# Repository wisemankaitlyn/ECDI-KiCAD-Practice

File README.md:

# KiCAD Practice with *Electronic Circuit Design Ideas*

I picked up an old textbook with a bunch of example circuits, and I'm using them to practice schematic and PCB layout with KiCAD.

1.  Digital Circuits
2.  Interface Circuits
3.  Timer Circuits
4.  Op-amp Circuits
5.  Amplifier Circuits
6.  Waveform Generators
7.  Phase-locked Loop Circuits
8.  Power Supply Circuits
9.  Voltage Regulator Circuits
10.  Battery Circuits
11.  Motor Control Circuits
12.  Encoders/Decoders
13.  Tester Circuits
14.  Miscellaneous Circuits

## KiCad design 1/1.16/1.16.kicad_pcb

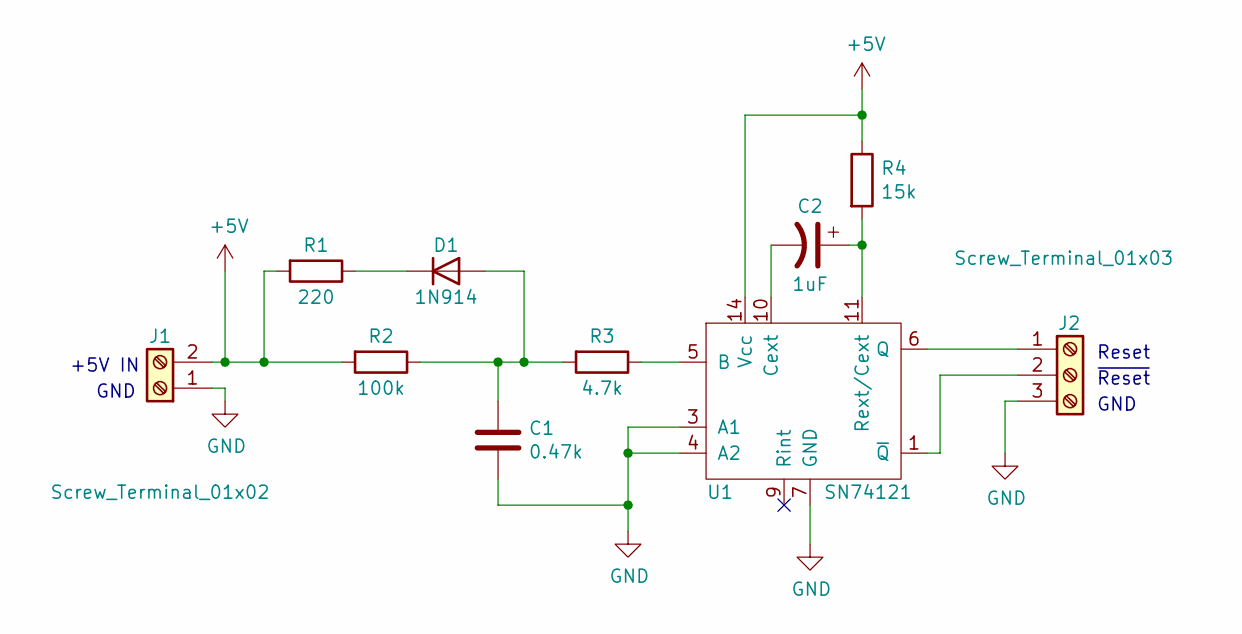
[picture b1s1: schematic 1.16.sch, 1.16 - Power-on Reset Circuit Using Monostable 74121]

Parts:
C1: 0.47k; C_Axial_L3.8mm_D2.6mm_P7.50mm_Horizontal
C2: 1uF; CP_Axial_L10.0mm_D4.5mm_P15.00mm_Horizontal
D1: 1N914; D_DO-35_SOD27_P7.62mm_Horizontal
J1: Screw_Terminal_01x02; TerminalBlock_bornier-2_P5.08mm
J2: Screw_Terminal_01x03; TerminalBlock_bornier-3_P5.08mm
R1: 220; R_Axial_DIN0207_L6.3mm_D2.5mm_P10.16mm_Horizontal
R2: 100k; R_Axial_DIN0207_L6.3mm_D2.5mm_P10.16mm_Horizontal
R3: 4.7k; R_Axial_DIN0207_L6.3mm_D2.5mm_P10.16mm_Horizontal
R4: 15k; R_Axial_DIN0207_L6.3mm_D2.5mm_P10.16mm_Horizontal
U1: SN74121; DIP-14_W7.62mm

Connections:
+5V: J1.2, R1.2, R2.2, R4.1, U1.14 (Vcc)
GND: C1.2, J1.1, J2.3, U1.3 (A1), U1.4 (A2), U1.7 (GND)
unnamed: C1.1, D1.2 (A), R2.1, R3.2
unnamed: C2.1, R4.2, U1.11 (Rext/Cext)
unnamed: C2.2, U1.10 (Cext)
unnamed: D1.1 (K), R1.1
unnamed: J2.1, U1.6 (Q)
unnamed: J2.2, U1.1 (~Q)
unnamed: R3.1, U1.5 (B)

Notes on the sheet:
+5V IN
GND
Reset
~Reset

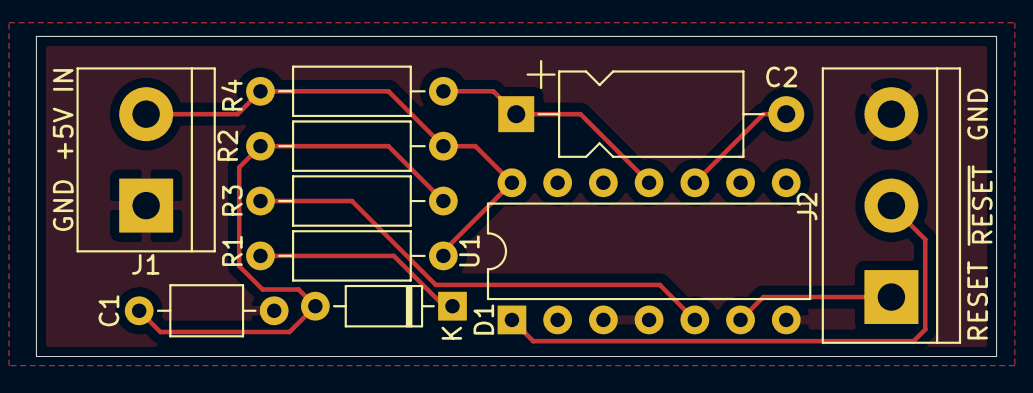
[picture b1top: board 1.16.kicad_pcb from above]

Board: 2 copper layers, 53.3 x 17.8 mm, 10 parts (0 on the bottom side), 9 nets.

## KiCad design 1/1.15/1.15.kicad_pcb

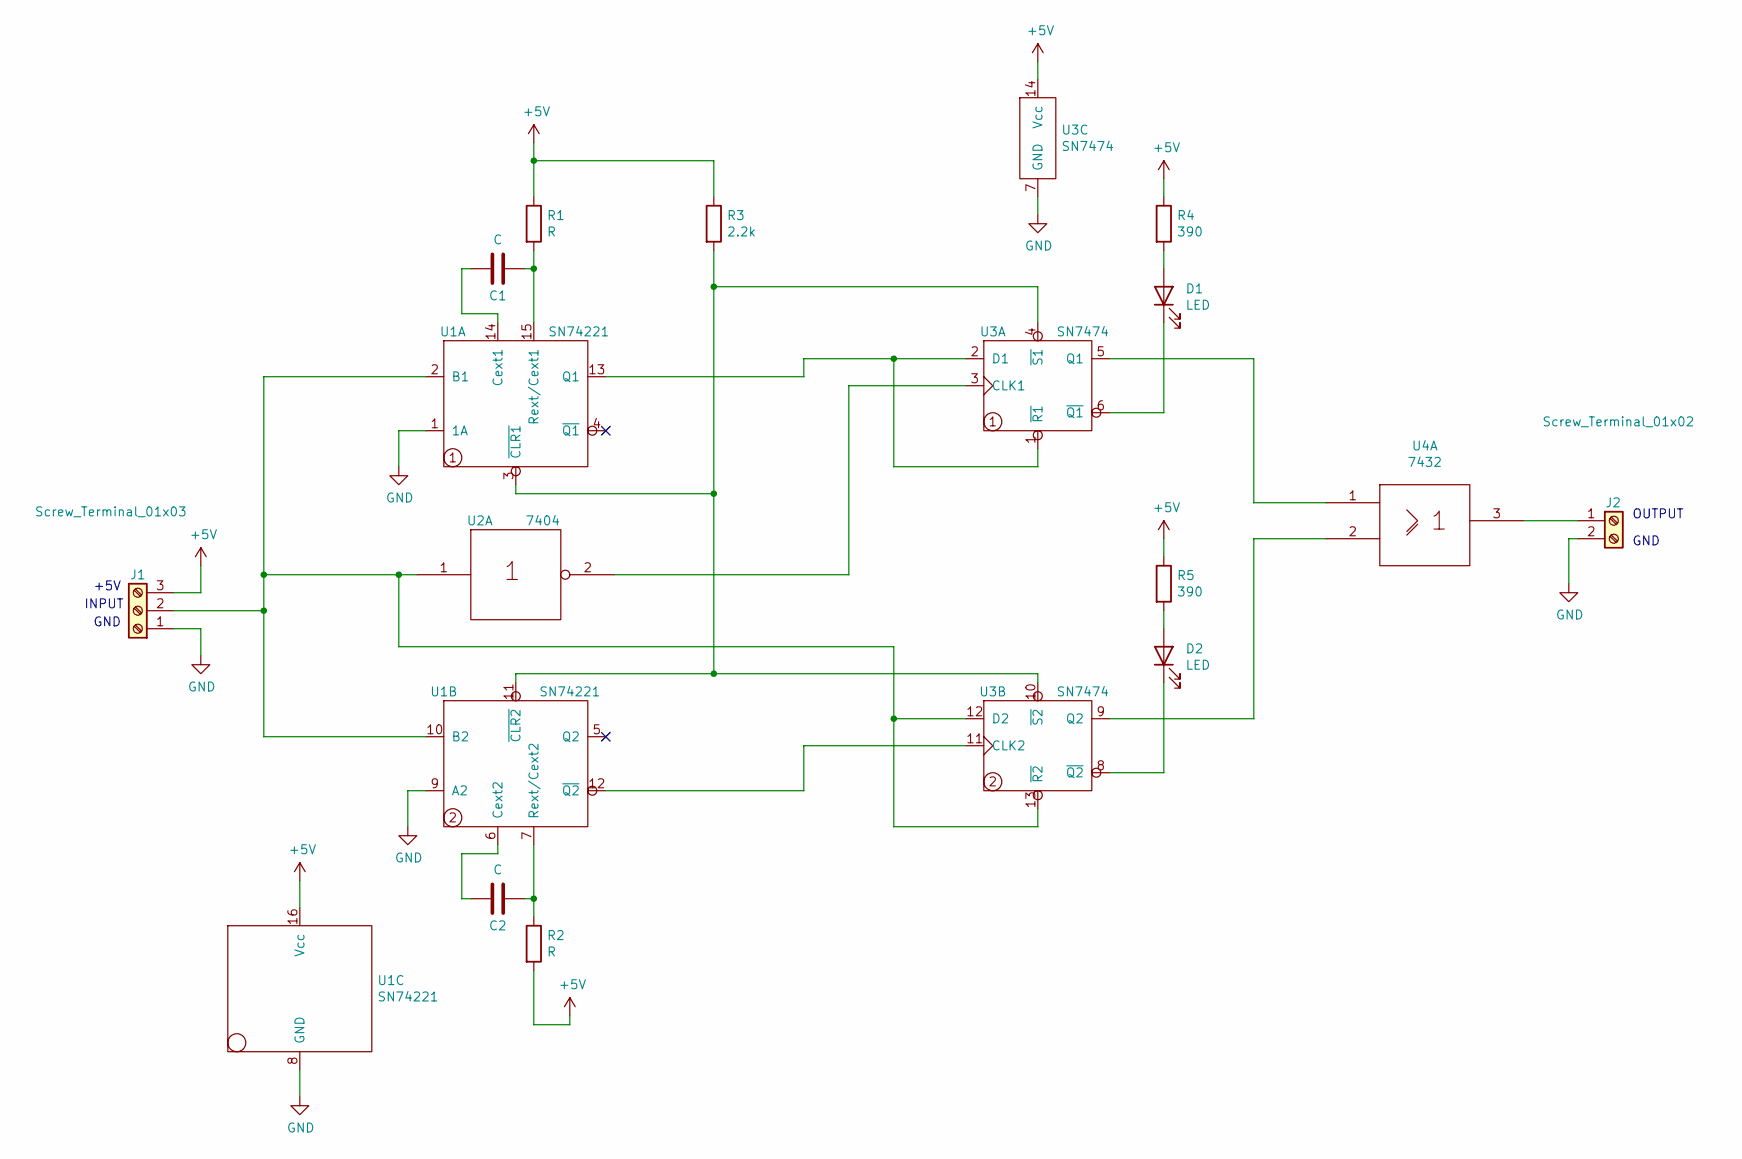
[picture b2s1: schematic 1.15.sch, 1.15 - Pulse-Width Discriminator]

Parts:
C1, C2: C; C_Axial_L3.8mm_D2.6mm_P7.50mm_Horizontal
D1, D2: LED; LED_D3.0mm
J1: Screw_Terminal_01x03; TerminalBlock_bornier-3_P5.08mm
J2: Screw_Terminal_01x02; TerminalBlock_bornier-2_P5.08mm
R1, R2: R; R_Axial_DIN0207_L6.3mm_D2.5mm_P10.16mm_Horizontal
R3: 2.2k; R_Axial_DIN0207_L6.3mm_D2.5mm_P10.16mm_Horizontal
R4, R5: 390; R_Axial_DIN0207_L6.3mm_D2.5mm_P10.16mm_Horizontal
U1: SN74221; DIP-16_W7.62mm
U2: 7404; DIP-14_W7.62mm
U3: SN7474; DIP-14_W7.62mm
U4: 7432; DIP-14_W7.62mm

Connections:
+5V: J1.3, R1.1, R2.2, R3.1, R4.1, R5.1, U1.16 (Vcc), U2.14 (Vcc), U3.14 (Vcc), U4.14 (Vcc)
GND: J1.1, J2.2, U1.1 (1A), U1.8 (GND), U1.9 (A2), U2.7 (Gnd), U3.7 (GND), U4.7 (Gnd)
unnamed: C1.1, R1.2, U1.15 (Rext/Cext1)
unnamed: C1.2, U1.14 (Cext1)
unnamed: C2.1, R2.1, U1.7 (Rext/Cext2)
unnamed: C2.2, U1.6 (Cext2)
unnamed: D1.1 (K), U3.6 (~Q1)
unnamed: D1.2 (A), R4.2
unnamed: D2.1 (K), U3.8 (~Q2)
unnamed: D2.2 (A), R5.2
unnamed: J1.2, U1.2 (B1), U1.10 (B2), U2.1, U3.12 (D2), U3.13 (~R2)
unnamed: J2.1, U4.3
unnamed: R3.2, U1.3 (~CLR1), U1.11 (~CLR2), U3.4 (~S1), U3.10 (~S2)
unnamed: U1.12 (~Q2), U3.11 (CLK2)
unnamed: U1.13 (Q1), U3.1 (~R1), U3.2 (D1)
unnamed: U2.2, U3.3 (CLK1)
unnamed: U3.5 (Q1), U4.1
unnamed: U3.9 (Q2), U4.2

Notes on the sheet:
+5V
INPUT
GND
OUTPUT

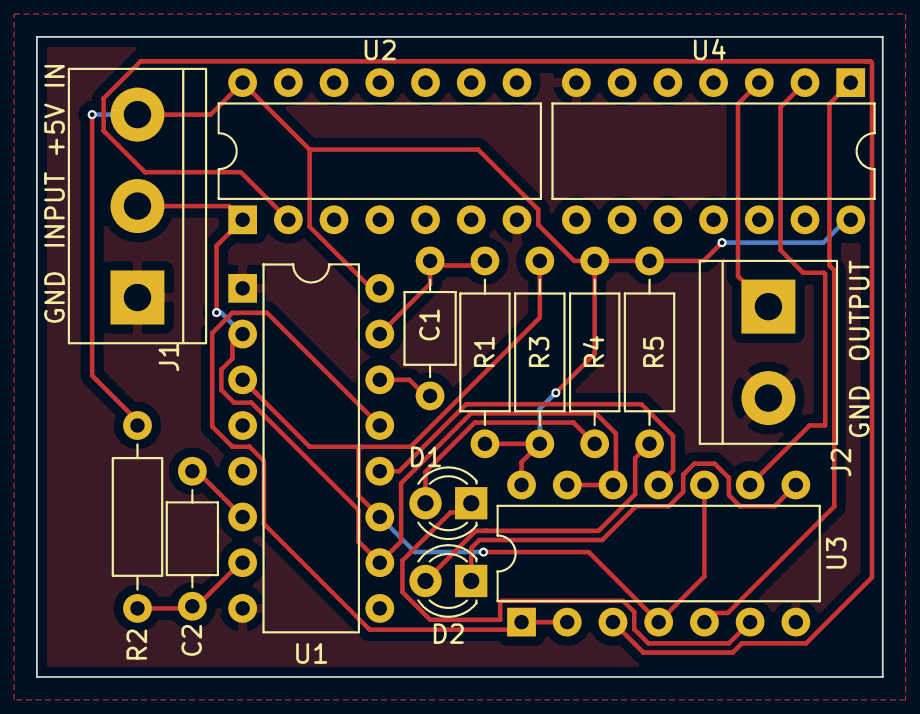
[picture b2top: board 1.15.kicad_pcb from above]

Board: 2 copper layers, 47.0 x 35.6 mm, 15 parts (0 on the bottom side), 18 nets.

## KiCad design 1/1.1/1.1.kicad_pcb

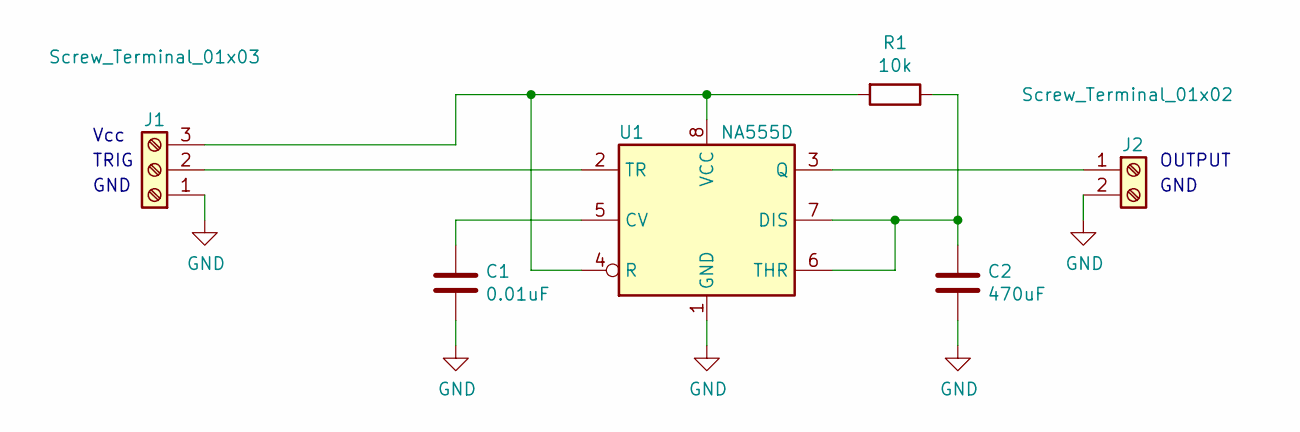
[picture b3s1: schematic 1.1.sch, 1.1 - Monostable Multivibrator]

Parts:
C1: 0.01uF; C_Axial_L5.1mm_D3.1mm_P10.00mm_Horizontal
C2: 470uF; C_Axial_L5.1mm_D3.1mm_P10.00mm_Horizontal
J1: Screw_Terminal_01x03; TerminalBlock_bornier-3_P5.08mm
J2: Screw_Terminal_01x02; TerminalBlock_bornier-2_P5.08mm
R1: 10k; R_Axial_DIN0207_L6.3mm_D2.5mm_P10.16mm_Horizontal
U1: NA555D; DIP-8_W7.62mm

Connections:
GND: C1.2, C2.2, J1.1, J2.2, U1.1 (GND)
unnamed: C1.1, U1.5 (CV)
unnamed: C2.1, R1.1, U1.6 (THR), U1.7 (DIS)
unnamed: J1.2, U1.2 (TR)
unnamed: J1.3, R1.2, U1.4 (R), U1.8 (VCC)
unnamed: J2.1, U1.3 (Q)

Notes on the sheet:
OUTPUT
GND
Vcc
TRIG

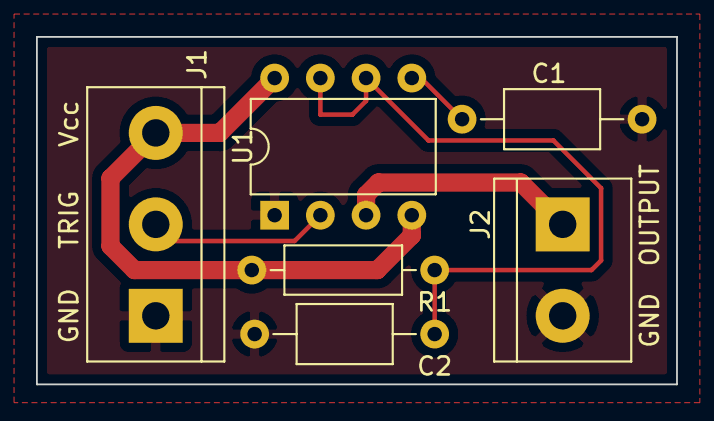
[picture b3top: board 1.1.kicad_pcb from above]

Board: 2 copper layers, 35.6 x 19.3 mm, 6 parts (0 on the bottom side), 6 nets.

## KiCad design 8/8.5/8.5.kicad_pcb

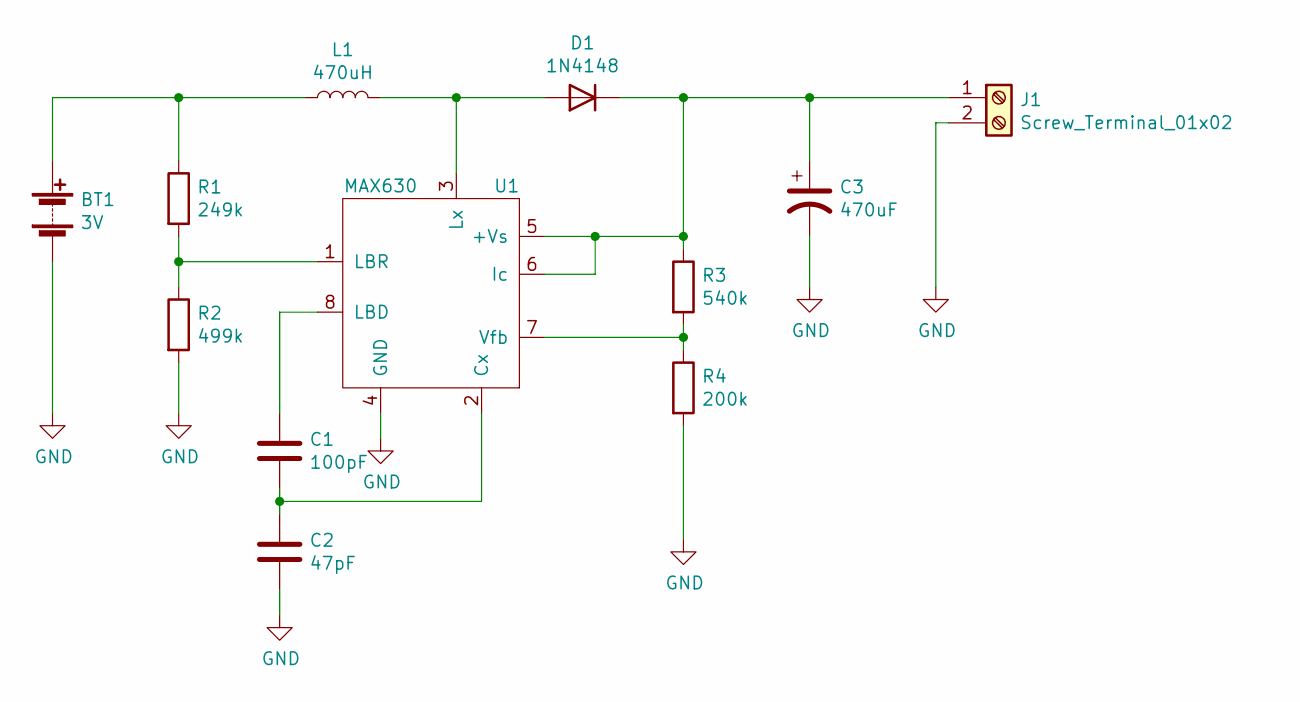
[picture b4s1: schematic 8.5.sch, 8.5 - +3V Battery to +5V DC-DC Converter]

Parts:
BT1: 3V; BatteryHolder_Keystone_1058_1x2032
C1: 100pF; C_Axial_L3.8mm_D2.6mm_P7.50mm_Horizontal
C2: 47pF; C_Axial_L3.8mm_D2.6mm_P7.50mm_Horizontal
C3: 470uF; C_Axial_L3.8mm_D2.6mm_P7.50mm_Horizontal
D1: 1N4148; D_DO-35_SOD27_P7.62mm_Horizontal
J1: Screw_Terminal_01x02; TerminalBlock_bornier-2_P5.08mm
L1: 470uH; L_Axial_L5.0mm_D3.6mm_P10.00mm_Horizontal_Murata_BL01RN1A2A2
R1: 249k; R_Axial_DIN0204_L3.6mm_D1.6mm_P5.08mm_Horizontal
R2: 499k; R_Axial_DIN0204_L3.6mm_D1.6mm_P5.08mm_Horizontal
R3: 540k; R_Axial_DIN0204_L3.6mm_D1.6mm_P5.08mm_Horizontal
R4: 200k; R_Axial_DIN0204_L3.6mm_D1.6mm_P5.08mm_Horizontal
U1: MAX630; MAX630CPA+_8-pin_CDIP

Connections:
GND: BT1.2 (-), C2.2, C3.2, J1.2, R2.2, R4.2, U1.4 (GND)
unnamed: BT1.1 (+), L1.1, R1.1
unnamed: C1.1, U1.8 (LBD)
unnamed: C1.2, C2.1, U1.2 (Cx)
unnamed: C3.1, D1.1 (K), J1.1, R3.1, U1.5 (+Vs), U1.6 (Ic)
unnamed: D1.2 (A), L1.2, U1.3 (Lx)
unnamed: R1.2, R2.1, U1.1 (LBR)
unnamed: R3.2, R4.1, U1.7 (Vfb)

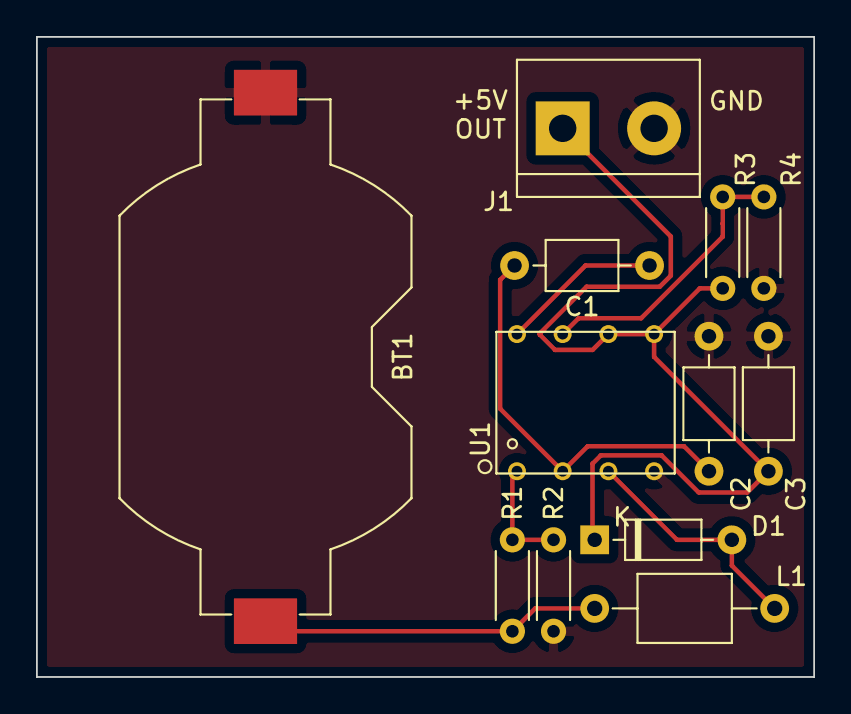
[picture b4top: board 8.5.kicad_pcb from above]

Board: 2 copper layers, 43.2 x 35.6 mm, 12 parts (0 on the bottom side), 8 nets.

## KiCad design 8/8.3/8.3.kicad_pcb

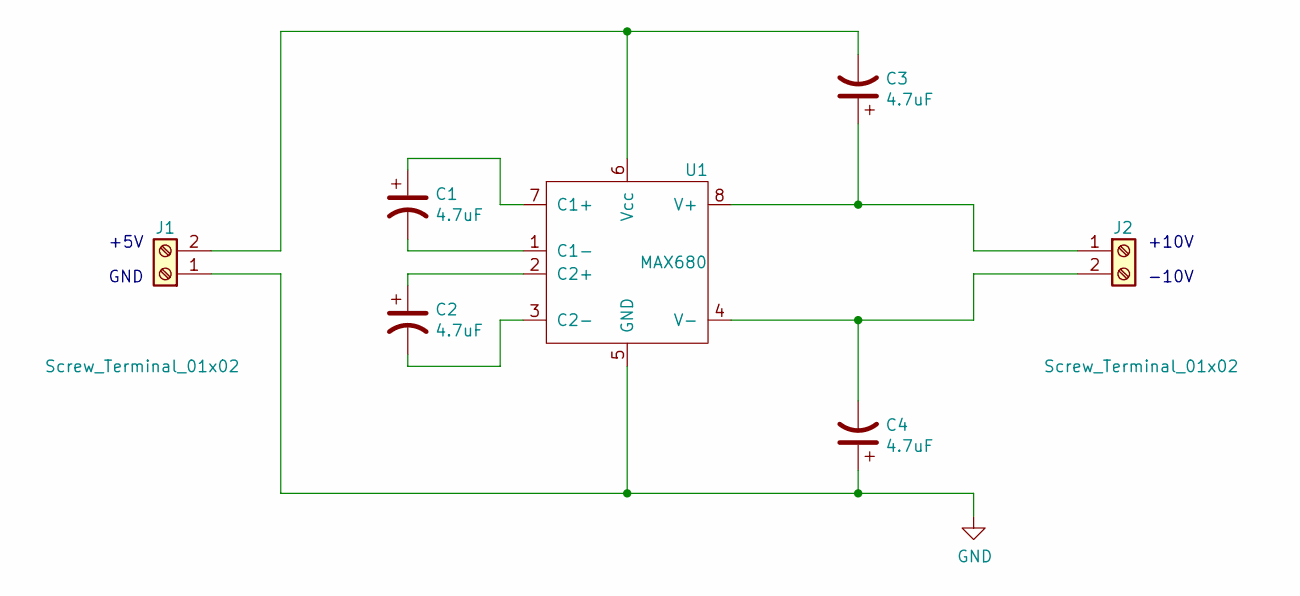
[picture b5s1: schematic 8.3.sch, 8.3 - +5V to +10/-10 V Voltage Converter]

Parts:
C1, C2, C3, C4: 4.7uF; CP_Axial_L10.0mm_D4.5mm_P15.00mm_Horizontal
J1, J2: Screw_Terminal_01x02; TerminalBlock_4Ucon_1x02_P3.50mm_Horizontal
U1: MAX680; MAX630CPA+_8-pin_CDIP

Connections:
GND: C4.1, J1.1, U1.5 (GND)
unnamed: C1.1, U1.7 (C1+)
unnamed: C1.2, U1.1 (C1-)
unnamed: C2.1, U1.2 (C2+)
unnamed: C2.2, U1.3 (C2-)
unnamed: C3.1, J2.1, U1.8 (V+)
unnamed: C3.2, J1.2, U1.6 (Vcc)
unnamed: C4.2, J2.2, U1.4 (V-)

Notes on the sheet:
+5V
GND
+10V
-10V

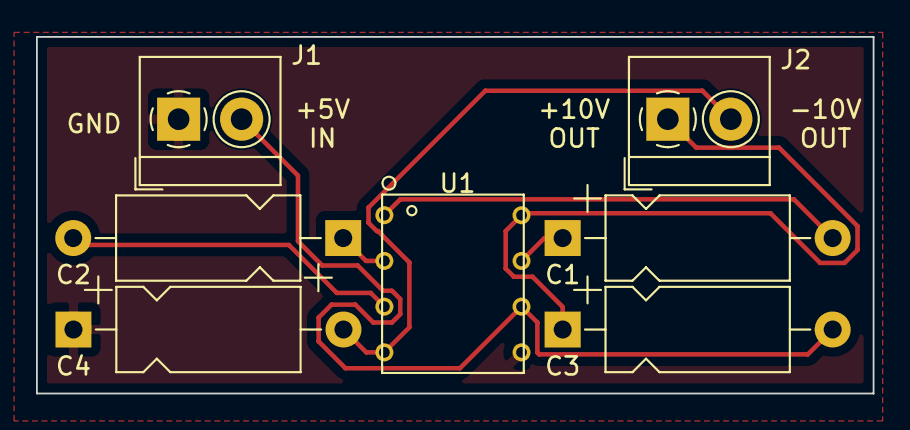
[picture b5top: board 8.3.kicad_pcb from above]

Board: 2 copper layers, 46.5 x 19.8 mm, 7 parts (0 on the bottom side), 8 nets.

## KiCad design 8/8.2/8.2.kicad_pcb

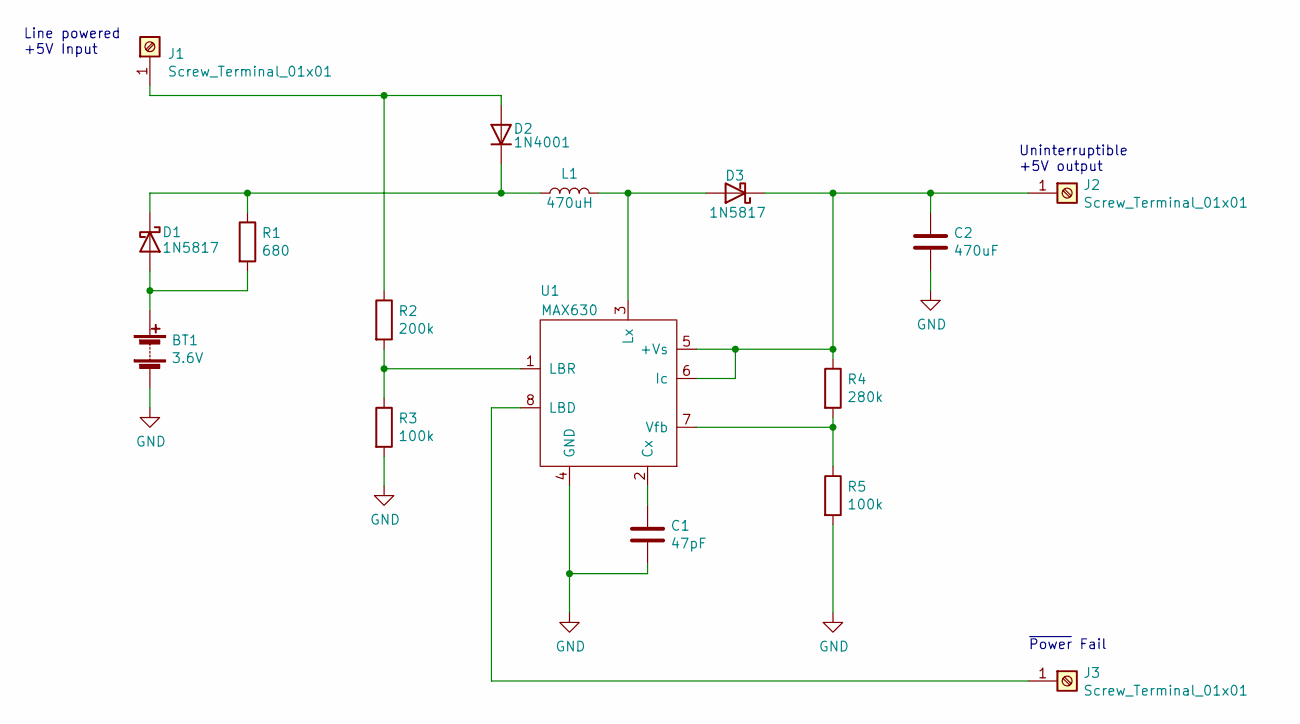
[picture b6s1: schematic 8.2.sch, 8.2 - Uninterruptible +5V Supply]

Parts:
BT1: 3.6V; BatteryHolder_Keystone_1042_1x18650
C1: 47pF; C_Axial_L5.1mm_D3.1mm_P7.50mm_Horizontal
C2: 470uF; C_Axial_L5.1mm_D3.1mm_P7.50mm_Horizontal
D1, D3: 1N5817; D_DO-41_SOD81_P10.16mm_Horizontal
D2: 1N4001; D_DO-41_SOD81_P10.16mm_Horizontal
J1, J2, J3: Screw_Terminal_01x01; TerminalBlock_MetzConnect_360271_1x01_Horizontal_ScrewM3.0_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
L1: 470uH; L_Axial_L5.3mm_D2.2mm_P7.62mm_Horizontal_Vishay_IM-1
R1: 680; R_Axial_DIN0207_L6.3mm_D2.5mm_P10.16mm_Horizontal
R2: 200k; R_Axial_DIN0207_L6.3mm_D2.5mm_P10.16mm_Horizontal
R3, R5: 100k; R_Axial_DIN0207_L6.3mm_D2.5mm_P10.16mm_Horizontal
R4: 280k; R_Axial_DIN0207_L6.3mm_D2.5mm_P10.16mm_Horizontal
U1: MAX630; MAX630CPA+_8-pin_CDIP

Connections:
GND: BT1.2 (-), C1.2, C2.2, R3.2, R5.2, U1.4 (GND)
unnamed: BT1.1 (+), D1.2 (A), R1.2
unnamed: C1.1, U1.2 (Cx)
unnamed: C2.1, D3.1 (K), J2.1, R4.1, U1.5 (+Vs), U1.6 (Ic)
unnamed: D1.1 (K), D2.1 (K), L1.1, R1.1
unnamed: D2.2 (A), J1.1, R2.1
unnamed: D3.2 (A), L1.2, U1.3 (Lx)
unnamed: J3.1, U1.8 (LBD)
unnamed: R2.2, R3.1, U1.1 (LBR)
unnamed: R4.2, R5.1, U1.7 (Vfb)

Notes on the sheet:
Uninterruptible +5V output
~Power Fail
Line powered +5V Input

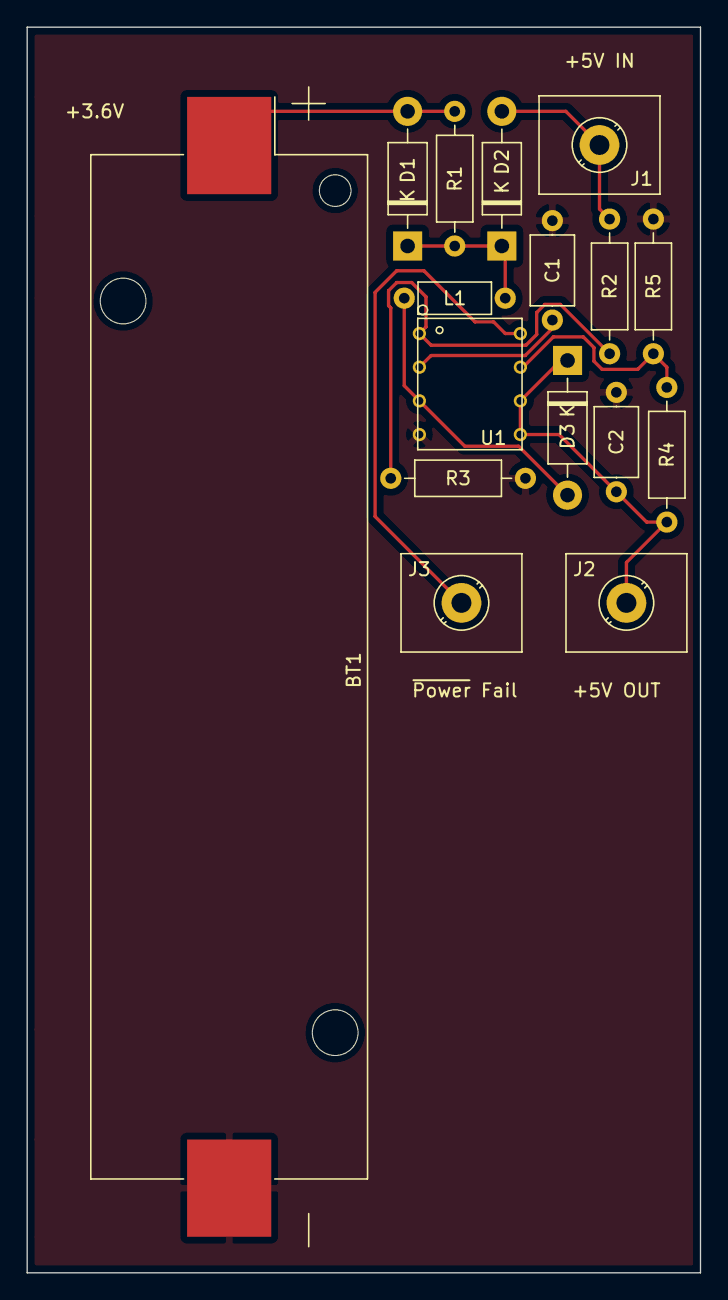
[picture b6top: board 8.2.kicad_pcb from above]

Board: 2 copper layers, 50.8 x 94.0 mm, 16 parts (0 on the bottom side), 10 nets.

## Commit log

2021-01-03 8.3 folder reorg
2021-01-04 1.15
2021-01-05 1.16
